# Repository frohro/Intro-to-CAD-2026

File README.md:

# Intro-to-CAD-2026

QSD SDR receiver board (WWU Intro to CAD) with versioned hardware and software.

## Layout

```text
v0.1/                  # First board revision
  Hardware/            # KiCad project for v0.1
  Software/SDR/        # MicroPython, Soapy, firmware/
v0.2/                  # Second board revision (CJC5340 option, etc.)
  Hardware/            # KiCad project for v0.2
  Software/SDR/        # MicroPython, Soapy, firmware/
Docs/                  # Plans, credits, restore notes
```

Pick the **root folder that matches the PCB silkscreen / board revision** you have.

| Board | Open KiCad | Software |
|-------|------------|----------|
| v0.1 | [v0.1/Hardware/Intro-to-CAD-2026.kicad_pro](v0.1/Hardware/Intro-to-CAD-2026.kicad_pro) | [v0.1/Software/SDR](v0.1/Software/SDR) |
| v0.2 | [v0.2/Hardware/Intro-to-CAD-2026.kicad_pro](v0.2/Hardware/Intro-to-CAD-2026.kicad_pro) | [v0.2/Software/SDR](v0.2/Software/SDR) |

Duplication between `v0.1` and `v0.2` is intentional so each board is self-contained.

## Firmware

Native Pico UAC1 projects live under each version's `Software/SDR/firmware/`.
Preferred v0.2 entry point: `v0.2/Software/SDR/firmware/2026_v0.2/`.
Re-sync notes: [Docs/FIRMWARE_RESTORE.md](Docs/FIRMWARE_RESTORE.md).

## History

- Tag `archive/pre-version-split` — layout before this reorg (student `Module_*` at repo root).
- Long-lived git branch `v0.2` held hardware work before the monorepo split; prefer paths under `v0.2/` on `master` going forward.
- Student module credits: [Docs/CREDITS.md](Docs/CREDITS.md).

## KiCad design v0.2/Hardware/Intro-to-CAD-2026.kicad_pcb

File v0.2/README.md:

# Board v0.2

## Hardware

Open [`Hardware/Intro-to-CAD-2026.kicad_pro`](Hardware/Intro-to-CAD-2026.kicad_pro).

Includes dual-ADC options (PCM1808 preferred; CJC5340 retained). Instructor
`Hardware/Frohne/` libs remain because the merged schematic references them.

## Software

| Path | Role |
|------|------|
| `Software/SDR/MicroPythonSDR/` | Pico MicroPython + Quisk helpers |
| `Software/SDR/Soapy-For-2026-Board/` | Soapy module |
| `Software/SDR/firmware/` | C UAC1 firmwares (PCM1808, CJC, Multi) — restore if empty |

Preferred firmware entry point once restored: `firmware/2026_v0.2/` (PCM1808 48/96).
CJC and Multi trees are kept for research even if PCM1808 is preferred on the bench.

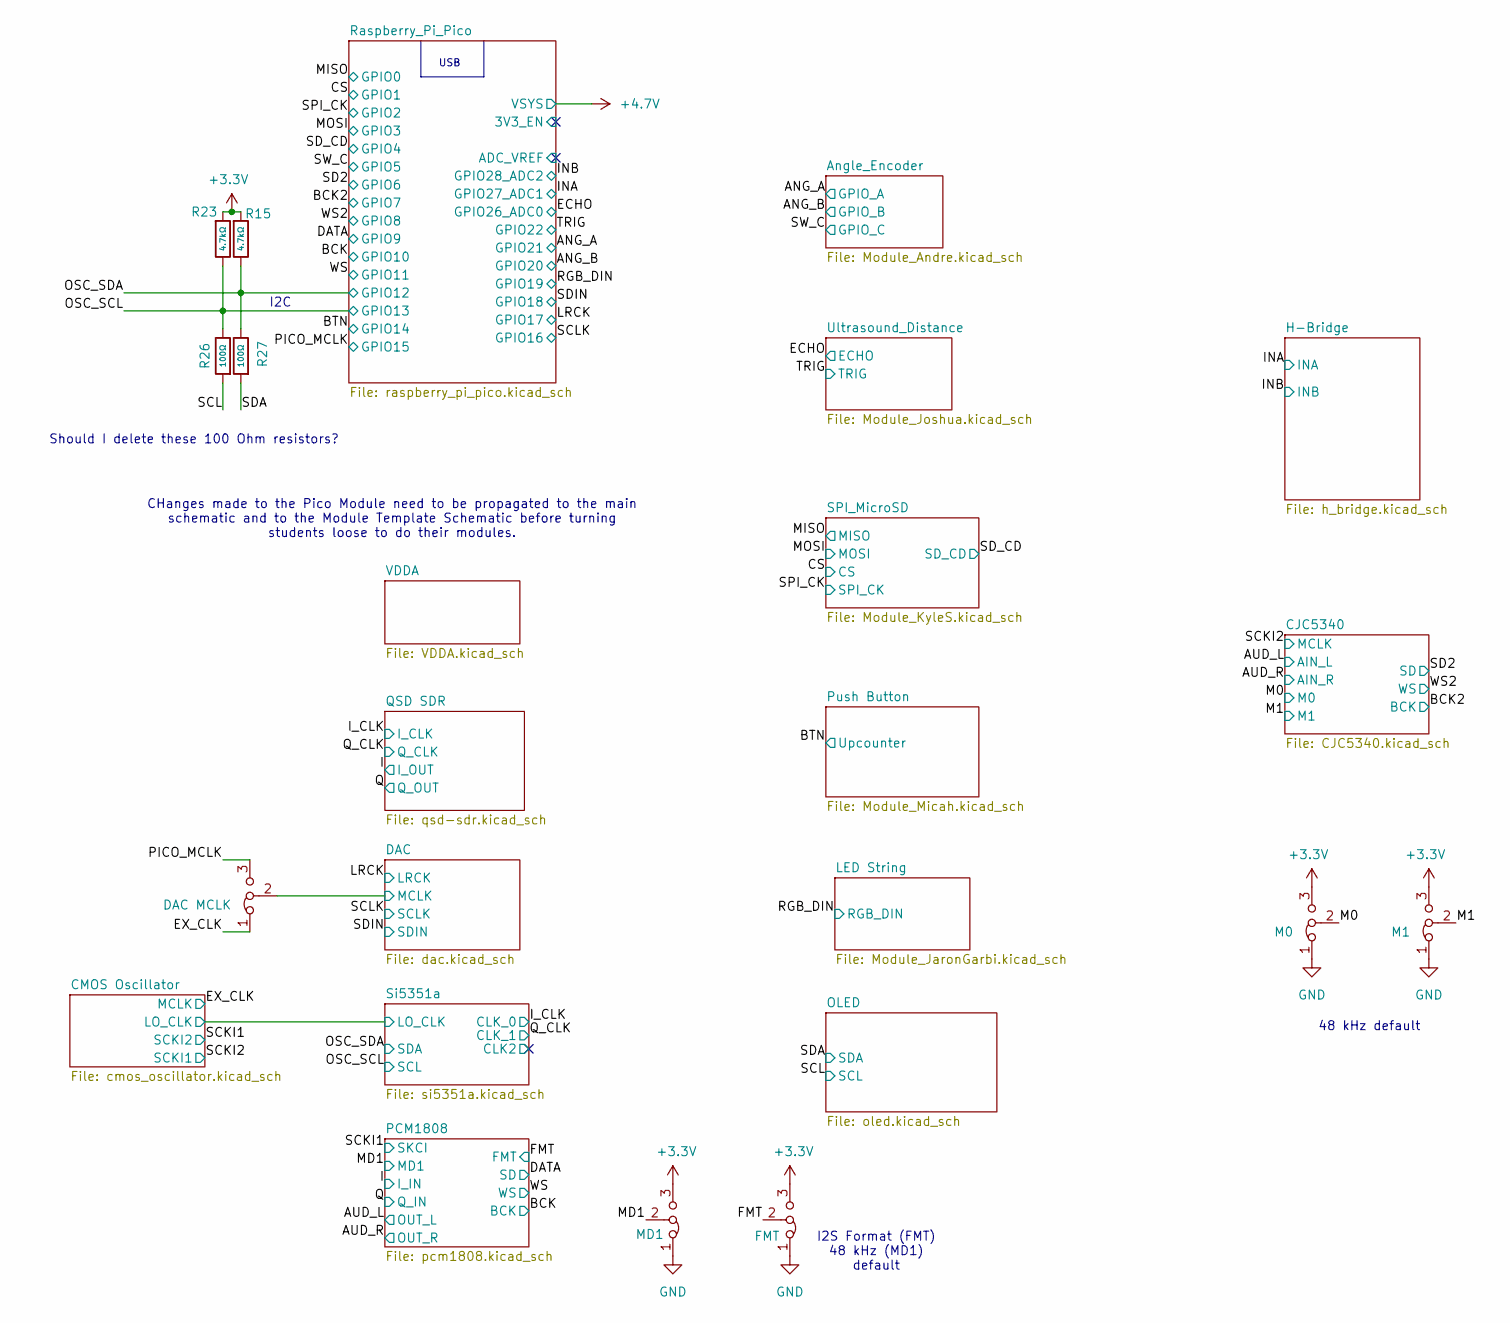
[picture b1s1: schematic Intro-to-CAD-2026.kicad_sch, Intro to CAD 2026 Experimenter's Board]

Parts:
JP6: DAC MCLK; SolderJumper-3_P1.3mm_Bridged12_RoundedPad1.0x1.5mm_NumberL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
JP11: M0; SolderJumper-3_P1.3mm_Bridged12_RoundedPad1.0x1.5mm_NumberL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
JP12: M1; SolderJumper-3_P1.3mm_Bridged12_RoundedPad1.0x1.5mm_NumberL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
JP13: FMT; SolderJumper-3_P1.3mm_Bridged12_RoundedPad1.0x1.5mm_NumberL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
JP14: MD1; SolderJumper-3_P1.3mm_Bridged12_RoundedPad1.0x1.5mm_NumberL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
R15, R23: 4.7kΩ; R_0805; Overload Voltage (Max) 150V; Tolerance ±1%; Part 0805W8F4701T5E; LCSC C17673
R26, R27: 100Ω; R_0805; Overload Voltage (Max) 150V; Tolerance ±1%; Part 0805W8F1000T5E; LCSC C17408

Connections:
+3.3V: JP11.3 (B), JP12.3 (B), JP13.3 (B), JP14.3 (B), R15.1, R23.1; also elsewhere on the board
/DAC/MCLK: JP6.2 (C); also elsewhere on the board
/EX_CLK: JP6.1 (A); also elsewhere on the board
/FMT: JP13.2 (C); also elsewhere on the board
/M0: JP11.2 (C); also elsewhere on the board
/M1: JP12.2 (C); also elsewhere on the board
/MD1: JP14.2 (C); also elsewhere on the board
/OSC_SCL: R23.2, R26.2; also elsewhere on the board
/OSC_SDA: R15.2, R27.2; also elsewhere on the board
/PICO_MCLK: JP6.3 (B); also elsewhere on the board
/SCL: R26.1; also elsewhere on the board
/SDA: R27.1; also elsewhere on the board
GND: JP11.1 (A), JP12.1 (A), JP13.1 (A), JP14.1 (A); also elsewhere on the board

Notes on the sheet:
CHanges made to the Pico Module need to be propagated to the main schematic and to the Module Template Schematic before turning students loose to do their modules.
Should I delete these 100 Ohm resistors?
I2S Format (FMT) 48 kHz (MD1) default
I2C
USB
48 kHz default

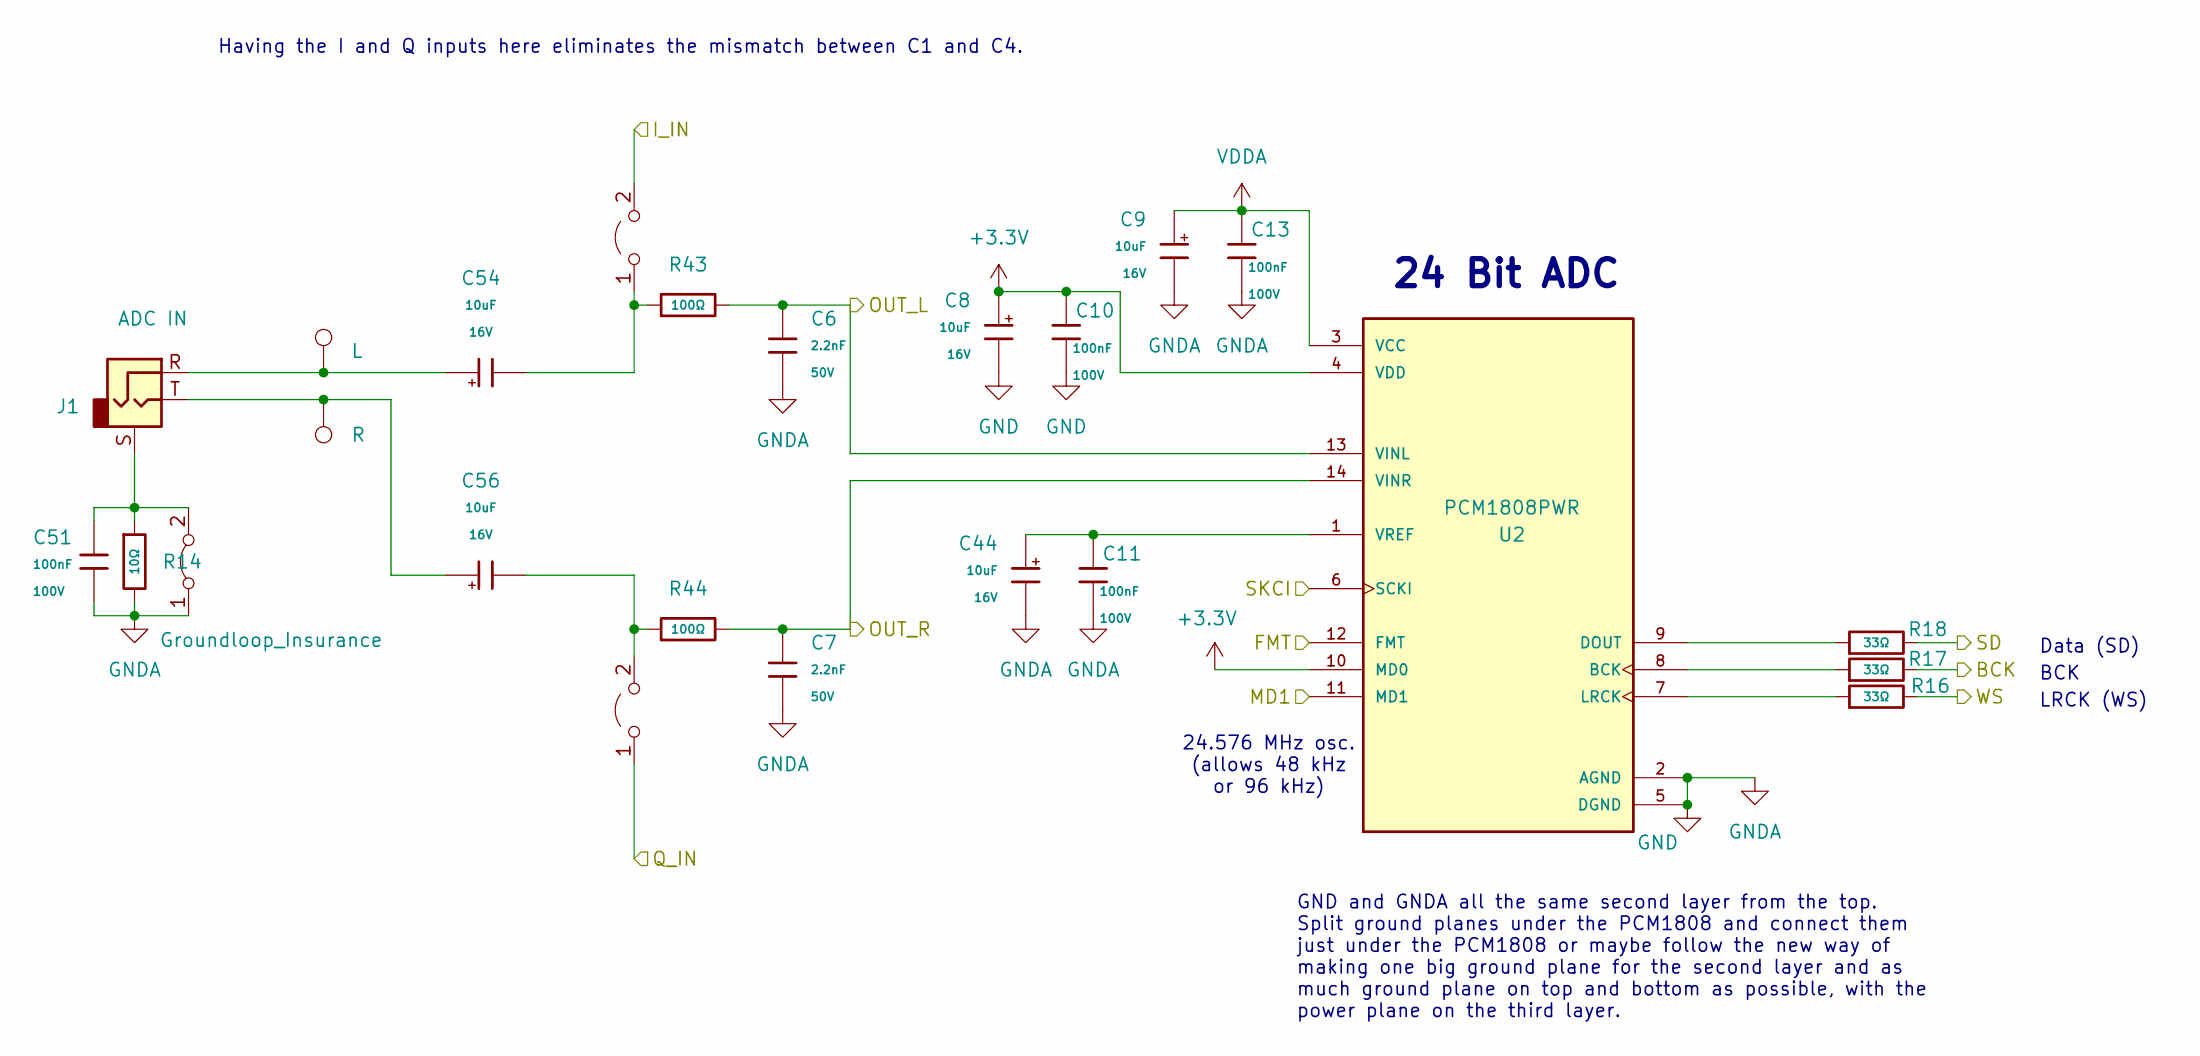
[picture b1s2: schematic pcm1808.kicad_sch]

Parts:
C6, C7: 2.2nF; C_0805; Voltage Rated 50V; Tolerance ±5%; Part CL21C222JBFNNNE; LCSC C28260
C8, C9, C44, C54, C56: 10uF; C_CASE-A-3216-18(mm); Tolerance ±10%; Rated Voltage 16V; Part TAJA106K016RNJ; LCSC C7171
C10, C11, C13, C51: 100nF; C_0805; Voltage Rated 100V; Tolerance ±10%; Part CL21B104KCFNNNE; LCSC C28233
J1: ADC IN; Jack_3.5mm_CUI_SJ-3523-SMT_Horizontal; LCSC C18594
JP18: I->ADC; SolderJumper-2_P1.3mm_Open_RoundedPad1.0x1.5mm
JP19: Q->ADC; SolderJumper-2_P1.3mm_Open_RoundedPad1.0x1.5mm
R14: 10Ω; R_0603; Overload Voltage (Max) 75V; Tolerance ±1%; Part 0603WAF100JT5E; LCSC C22859
R16, R17, R18: 33Ω; R_0805; Overload Voltage (Max) 150V; Tolerance ±1%; Part 0805W8F330JT5E; LCSC C17634
R43, R44: 100Ω; R_0603; Overload Voltage (Max) 75V; Tolerance ±1%; Part 0603WAF1000T5E; LCSC C22775
TP1: L; TestPoint_THTPad_D2.0mm_Drill1.0mm
TP2: R; TestPoint_THTPad_D2.0mm_Drill1.0mm
U2: PCM1808PWR; TSSOP-14_4.4x5mm_P0.65mm; PARTREV B; LCSC C55513
e4: Groundloop_Insurance; SolderJumper-2_P1.3mm_Bridged_RoundedPad1.0x1.5mm

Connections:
+3.3V: C8.1, C10.2, U2.4 (VDD), U2.10 (MD0); also elsewhere on the board
/AUD_L: C6.1, R43.2, U2.13 (VINL); also elsewhere on the board
/AUD_R: C7.1, R44.2, U2.14 (VINR); also elsewhere on the board
/BCK: R17.2; also elsewhere on the board
/DATA: R18.2; also elsewhere on the board
/FMT: U2.12 (FMT); also elsewhere on the board
/I: JP18.2 (B); also elsewhere on the board
/MD1: U2.11 (MD1); also elsewhere on the board
/Q: JP19.1 (A); also elsewhere on the board
/SCKI1: U2.6 (SCKI); also elsewhere on the board
/WS: R16.2; also elsewhere on the board
GND: C6.2, C7.2, C8.2, C9.2, C10.1, C11.1, C13.1, C44.2, C51.1, R14.2, U2.2 (AGND), U2.5 (DGND), e4.1 (A); also elsewhere on the board
unnamed: C54.1, J1.R, TP1.1 (1_1)
unnamed: C56.1, J1.T, TP2.1 (1_1)
unnamed: C54.2, JP18.1 (A), R43.1
unnamed: C56.2, JP19.2 (B), R44.1
unnamed: R17.1, U2.8 (BCK)
unnamed: R18.1, U2.9 (DOUT)
unnamed: R16.1, U2.7 (LRCK)
unnamed: C11.2, C44.1, U2.1 (VREF)
unnamed: C51.2, J1.S, R14.1, e4.2 (B)
VDDA: C9.1, C13.2, U2.3 (VCC); also elsewhere on the board

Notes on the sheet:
24 Bit ADC
Data (SD)
24.576 MHz osc. (allows 48 kHz or 96 kHz)
BCK
GND and GNDA all the same second layer from the top. Split ground planes under the PCM1808 and connect them just under the PCM1808 or maybe follow the new way of making one big ground plane for the second layer and as much ground plane on top and bottom as possible, with the power plane on the thir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
Having the I and Q inputs here eliminates the mismatch between C1 and C4.
LRCK (WS)

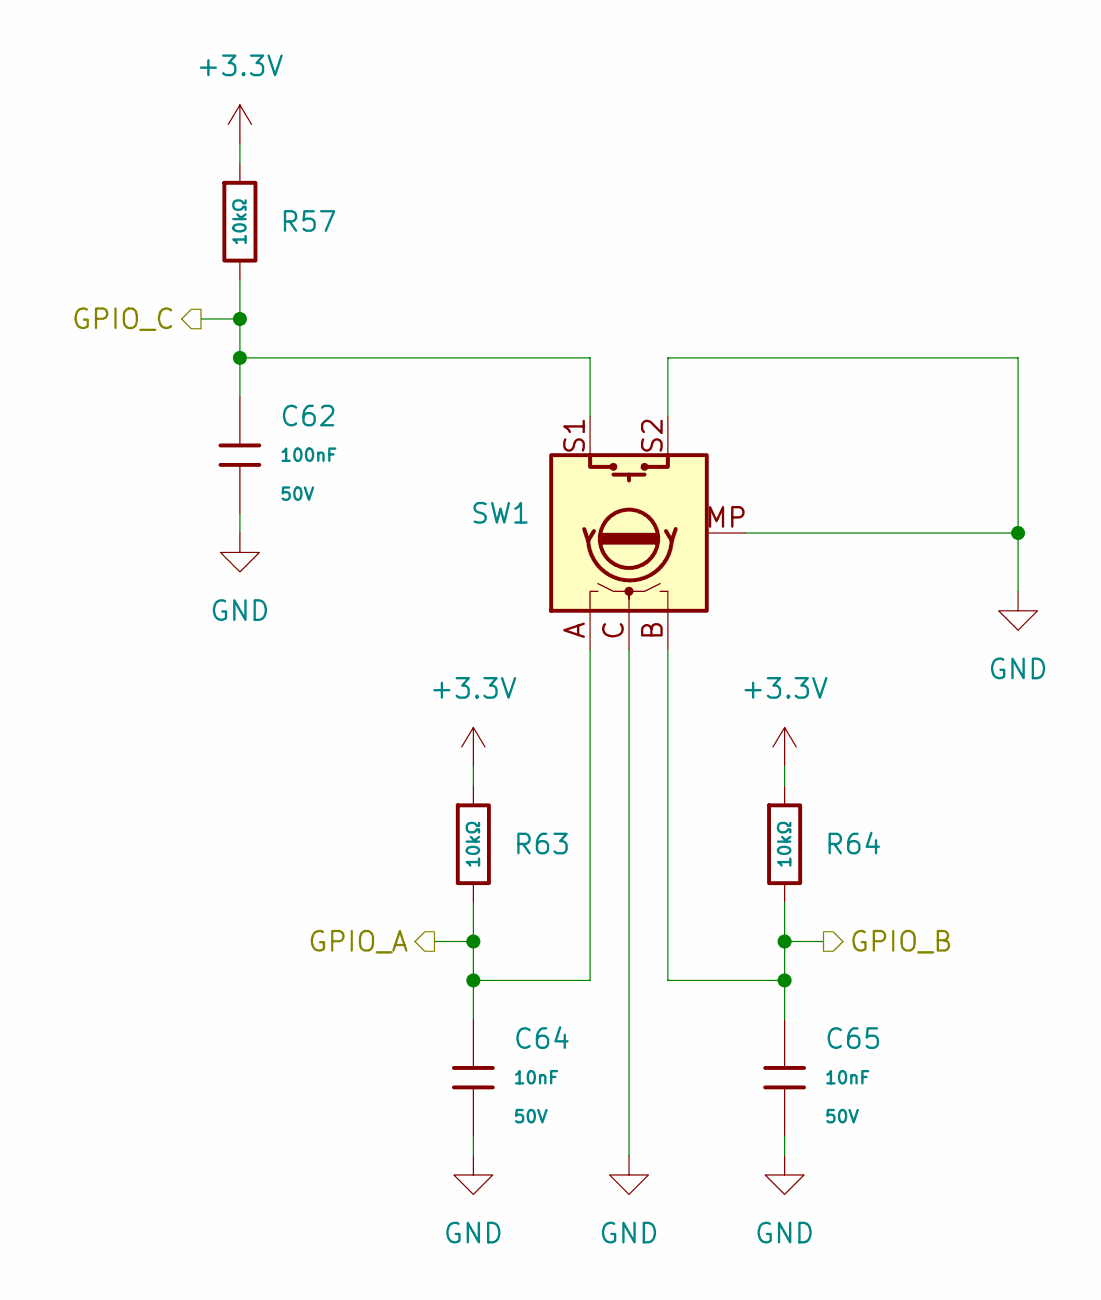
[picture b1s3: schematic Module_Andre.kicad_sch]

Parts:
C62: 100nF; C_0402; Voltage Rated 50V; Tolerance ±10%; Part CL05B104KB54PNC; LCSC C307331
C64, C65: 10nF; C_0402; Voltage Rated 50V; Tolerance ±10%; Part CL05B103KB5NNNC; LCSC C15195
R57, R63, R64: 10kΩ; R_0402; Overload Voltage (Max) 50V; Tolerance ±1%; Part 0402WGF1002TCE; LCSC C25744
SW1: RotaryEncoder_Switch_MP; RotaryEncoder_Alps_EC11E-Switch_Vertical_H20mm; LCSC C202365

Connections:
+3.3V: R57.1, R63.1, R64.1; also elsewhere on the board
/ANG_A: C64.1, R63.2, SW1.A; also elsewhere on the board
/ANG_B: C65.1, R64.2, SW1.B; also elsewhere on the board
/SW_C: C62.1, R57.2, SW1.S1; also elsewhere on the board
GND: C62.2, C64.2, C65.2, SW1.C, SW1.MP, SW1.S2; also elsewhere on the board

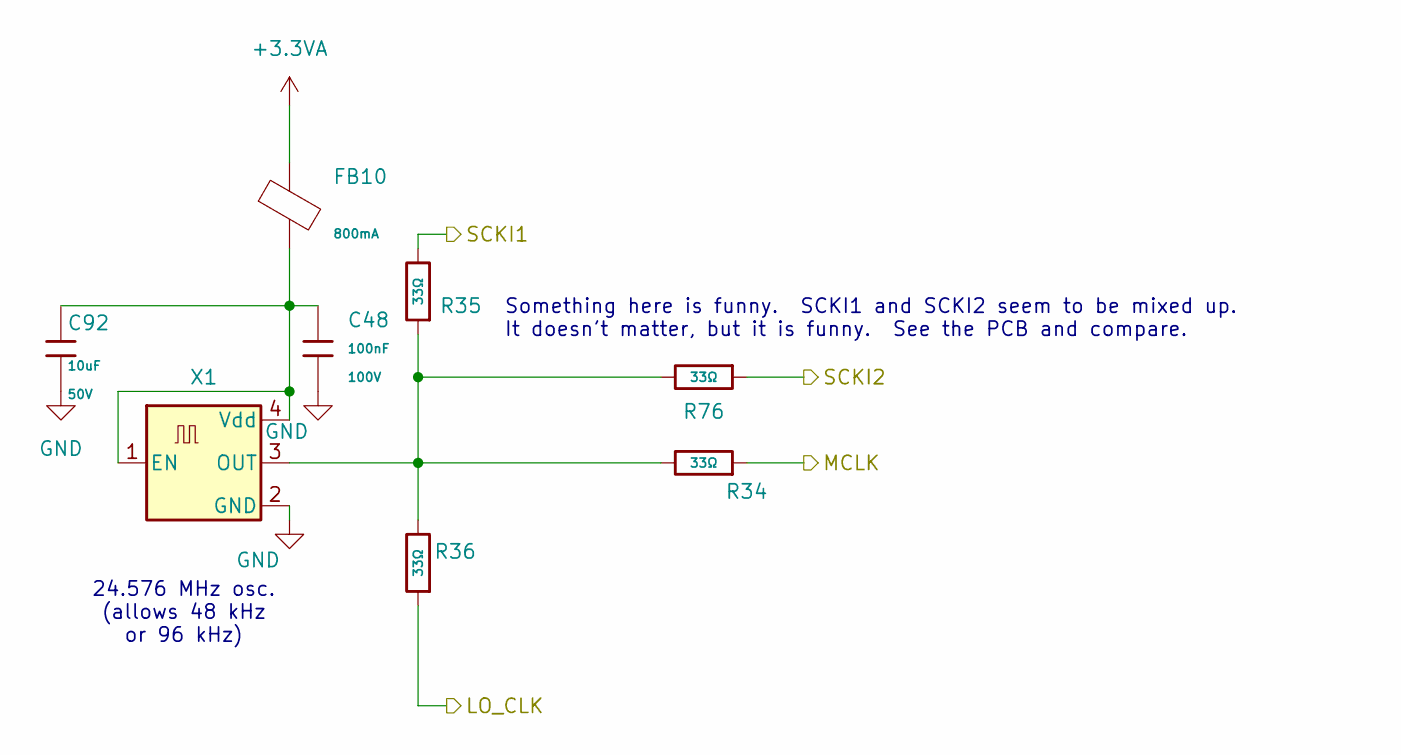
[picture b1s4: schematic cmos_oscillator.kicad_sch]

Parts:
C48: 100nF; C_0805; Voltage Rated 100V; Tolerance ±10%; Part CL21B104KCFNNNE; LCSC C28233
C92: 10uF; C_1206; Voltage Rated 50V; Tolerance ±10%; Part CL31A106KBHNNNE; LCSC C13585
FB10: FB_0805; Current Rating 800mA; Tolerance ±25%; Part GZ2012D101TF; LCSC C1015
R34, R35, R36, R76: 33Ω; R_0805; Overload Voltage (Max) 150V; Tolerance ±1%; Part 0805W8F330JT5E; LCSC C17634
X1: YC24.576MUBCE2O; Oscillator_SMD_Abracon_ASE-4Pin_3.2x2.5mm; LCSC C52204801

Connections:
+3.3VA: FB10.1; also elsewhere on the board
/CMOS Oscillator/LO_CLK: R36.1; also elsewhere on the board
/EX_CLK: R34.1; also elsewhere on the board
/SCKI1: R76.1; also elsewhere on the board
/SCKI2: R35.2; also elsewhere on the board
GND: C48.2, C92.2, X1.2 (GND); also elsewhere on the board
unnamed: C48.1, C92.1, FB10.2, X1.1 (EN), X1.4 (Vdd)
unnamed: R34.2, R35.1, R36.2, R76.2, X1.3 (OUT)

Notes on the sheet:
Something here is funny. SCKI1 and SCKI2 seem to be mixed up. It doesn't matter, but it is funny. See the PCB and compare.
24.576 MHz osc. (allows 48 kHz or 96 kHz)

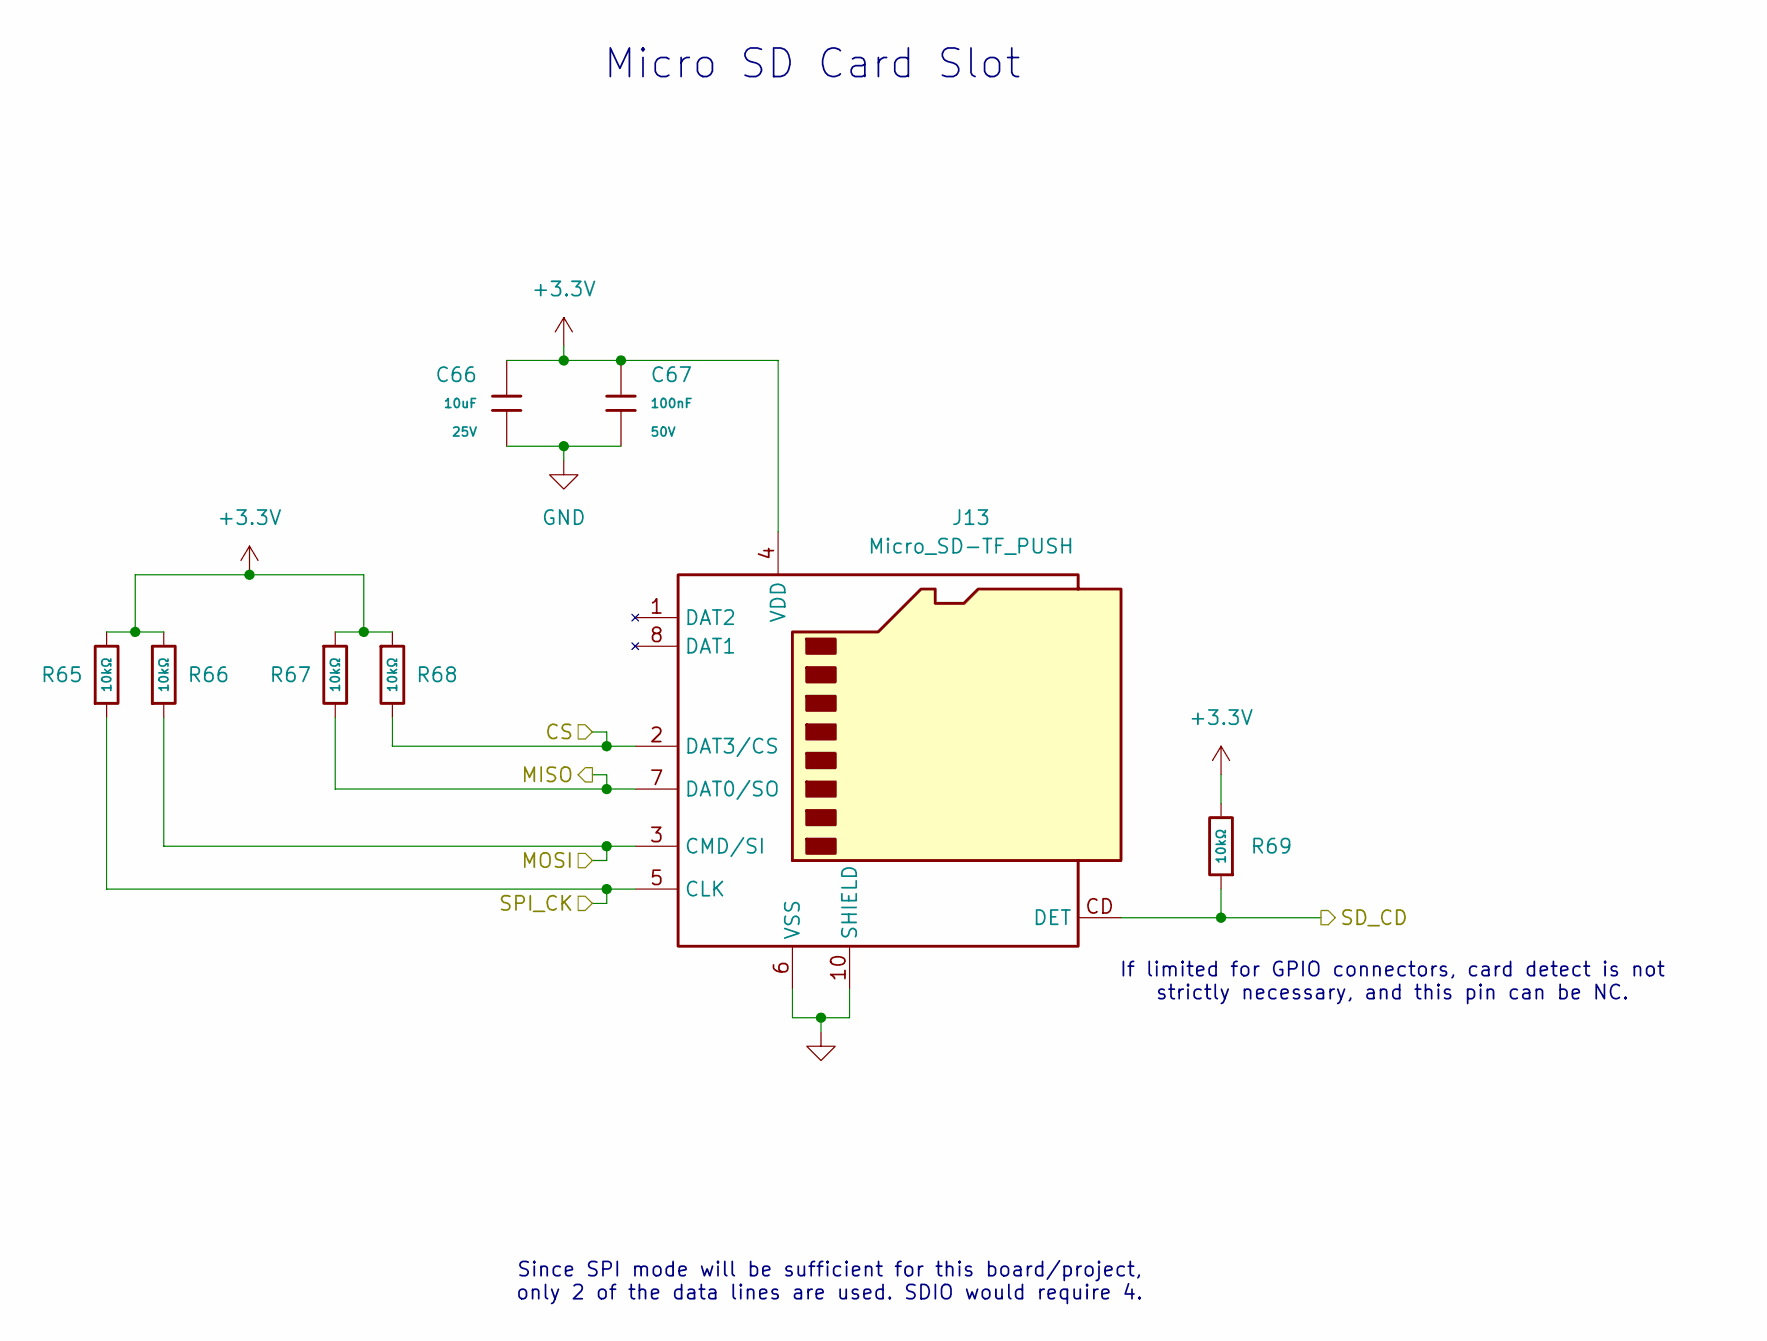
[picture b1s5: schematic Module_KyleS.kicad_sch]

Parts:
C66: 10uF; C_0805; Voltage Rated 25V; Tolerance ±10%; Part CL21A106KAYNNNE; LCSC C15850
C67: 100nF; C_0603; Voltage Rated 50V; Tolerance ±10%; Part CC0603KRX7R9BB104; LCSC C14663
J13: Micro_SD-TF_PUSH; TF-SMD_TF-PUSH; LCSC C393941
R65, R66, R67, R68, R69: 10kΩ; R_0603; Overload Voltage (Max) 75V; Tolerance ±1%; Part 0603WAF1002T5E; LCSC C25804

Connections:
+3.3V: C66.1, C67.1, J13.4 (VDD), R65.2, R66.2, R67.1, R68.1, R69.2; also elsewhere on the board
/CS: J13.2 (DAT3/CS), R68.2; also elsewhere on the board
/MISO: J13.7 (DAT0/SO), R67.2; also elsewhere on the board
/MOSI: J13.3 (CMD/SI), R66.1; also elsewhere on the board
/SD_CD: J13.CD (DET), R69.1; also elsewhere on the board
/SPI_CK: J13.5 (CLK), R65.1; also elsewhere on the board
GND: C66.2, C67.2, J13.6 (VSS), J13.10 (SHIELD), J13.11 (SHIELD), J13.12 (SHIELD), J13.13 (SHIELD); also elsewhere on the board

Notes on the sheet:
Since SPI mode will be sufficient for this board/project, only 2 of the data lines are used. SDIO would require 4.
Micro SD Card Slot
If limited for GPIO connectors, card detect is not strictly necessary, and this pin can be NC.

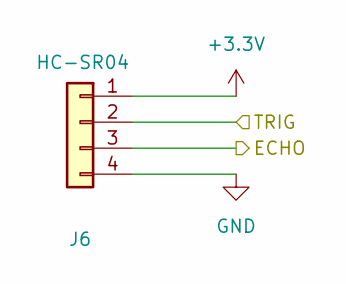
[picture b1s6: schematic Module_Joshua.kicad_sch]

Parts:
J6: HC-SR04; PinSocket_1x04_P2.54mm_Vertical; LCSC C2718488

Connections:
+3.3V: J6.1; also elsewhere on the board
/ECHO: J6.3; also elsewhere on the board
/TRIG: J6.2; also elsewhere on the board
GND: J6.4; also elsewhere on the board

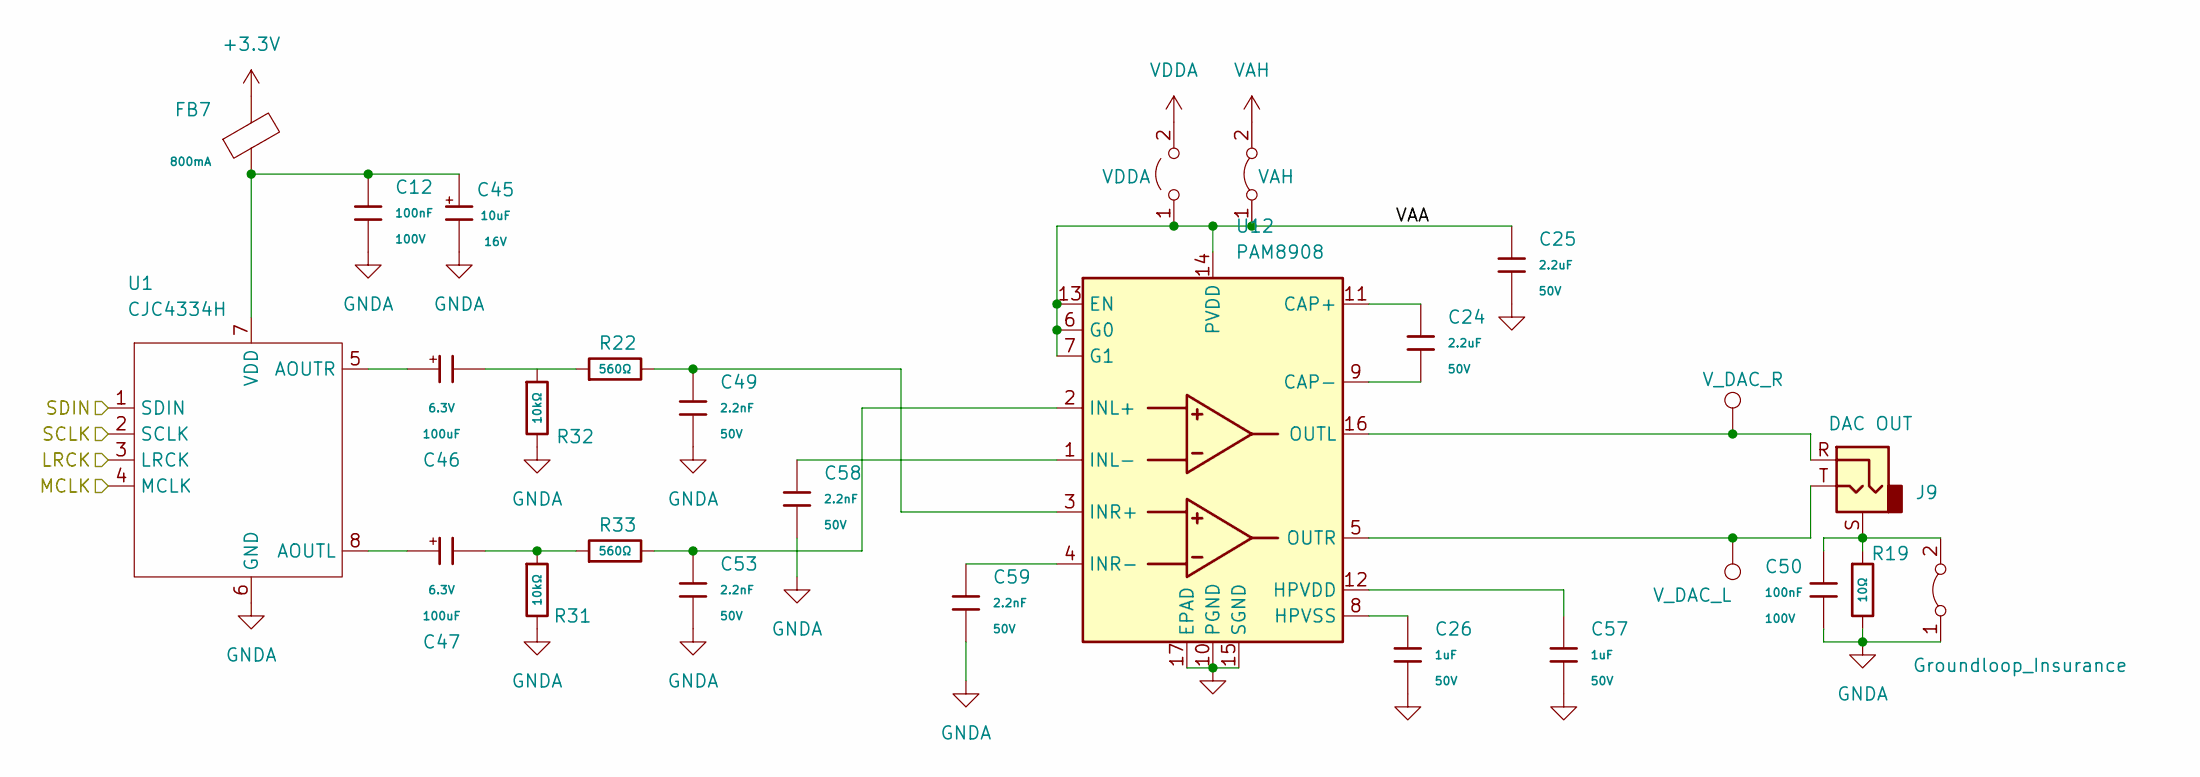
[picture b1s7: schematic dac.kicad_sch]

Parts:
C12, C50: 100nF; C_0805; Voltage Rated 100V; Tolerance ±10%; Part CL21B104KCFNNNE; LCSC C28233
C24, C25: 2.2uF; C_0805; Voltage Rated 50V; Tolerance ±10%; Part CL21A225KBQNNNE; LCSC C377773
C26, C57: 1uF; C_0805; Voltage Rated 50V; Tolerance ±10%; Part CL21B105KBFNNNE; LCSC C28323
C45: 10uF; C_CASE-A-3216-18(mm); Tolerance ±10%; Rated Voltage 16V; Part TAJA106K016RNJ; LCSC C7171
C46, C47: 100uF; C_CASE-B-3528-21(mm); Tolerance ±10%; Rated Voltage 6.3V; Part TAJB107K006RNJ; LCSC C16133
C49, C53, C58, C59: 2.2nF; C_0805; Voltage Rated 50V; Tolerance ±5%; Part CL21C222JBFNNNE; LCSC C28260
FB7: FB_0805; Current Rating 800mA; Tolerance ±25%; Part GZ2012D101TF; LCSC C1015
J9: 3.5mm_Jack; Jack_3.5mm_CUI_SJ-3523-SMT_Horizontal; LCSC C18594
JP3: VDDA; SolderJumper-2_P1.3mm_Open_RoundedPad1.0x1.5mm
R19: 10Ω; R_0603; Overload Voltage (Max) 75V; Tolerance ±1%; Part 0603WAF100JT5E; LCSC C22859
R22, R33: 560Ω; R_0805; Overload Voltage (Max) 150V; Tolerance ±1%; Part 0805W8F5600T5E; LCSC C28636
R31, R32: 10kΩ; R_0805; Overload Voltage (Max) 150V; Tolerance ±1%; Part 0805W8F1002T5E; LCSC C17414
TP8: V_DAC_R; TestPoint_THTPad_D2.0mm_Drill1.0mm
TP9: V_DAC_L; TestPoint_THTPad_D2.0mm_Drill1.0mm
U1: CJC4334H; SOIC-8_3.9x4.9mm_P1.27mm; LCSC C41417670
U12: PAM8908; QFN-16-1EP_3x3mm_P0.5mm_EP1.7x1.7mm; LCSC C33233
e2: VAH; SolderJumper-2_P1.3mm_Bridged_RoundedPad1.0x1.5mm
e3: Groundloop_Insurance; SolderJumper-2_P1.3mm_Bridged_RoundedPad1.0x1.5mm

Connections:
+3.3V: FB7.2; also elsewhere on the board
+4.7V: e2.2 (B); also elsewhere on the board
/DAC/MCLK: U1.4 (MCLK); also elsewhere on the board
/DAC/VAA: C25.1, JP3.1 (A), U12.6 (G0), U12.7 (G1), U12.13 (EN), U12.14 (PVDD), e2.1 (A)
/LRCK: U1.3 (LRCK); also elsewhere on the board
/SCLK: U1.2 (SCLK); also elsewhere on the board
/SDIN: U1.1 (SDIN); also elsewhere on the board
GND: C12.2, C25.2, C26.2, C45.2, C49.2, C50.1, C53.2, C57.2, C58.2, C59.2, R19.2, R31.2, R32.2, U1.6 (GND), U12.10 (PGND), U12.15 (SGND), U12.17 (EPAD), e3.1 (A); also elsewhere on the board
unnamed: C46.2, R22.1
unnamed: C47.2, R31.1, R33.1
unnamed: C47.1, U1.8 (AOUTL)
unnamed: C46.1, U1.5 (AOUTR)
unnamed: C12.1, C45.1, FB7.1, U1.7 (VDD)
unnamed: C24.1, U12.11 (CAP+)
unnamed: C24.2, U12.9 (CAP-)
unnamed: C57.1, U12.12 (HPVDD)
unnamed: C26.1, U12.8 (HPVSS)
unnamed: C53.1, R33.2, U12.2 (INL+)
unnamed: C58.1, U12.1 (INL-)
unnamed: C49.1, R22.2, U12.3 (INR+)
unnamed: C59.1, U12.4 (INR-)
unnamed: J9.R, TP8.1 (1_1), U12.16 (OUTL)
unnamed: J9.T, TP9.1 (1_1), U12.5 (OUTR)
unnamed: C50.2, J9.S, R19.1, e3.2 (B)
VDDA: JP3.2 (B); also elsewhere on the board

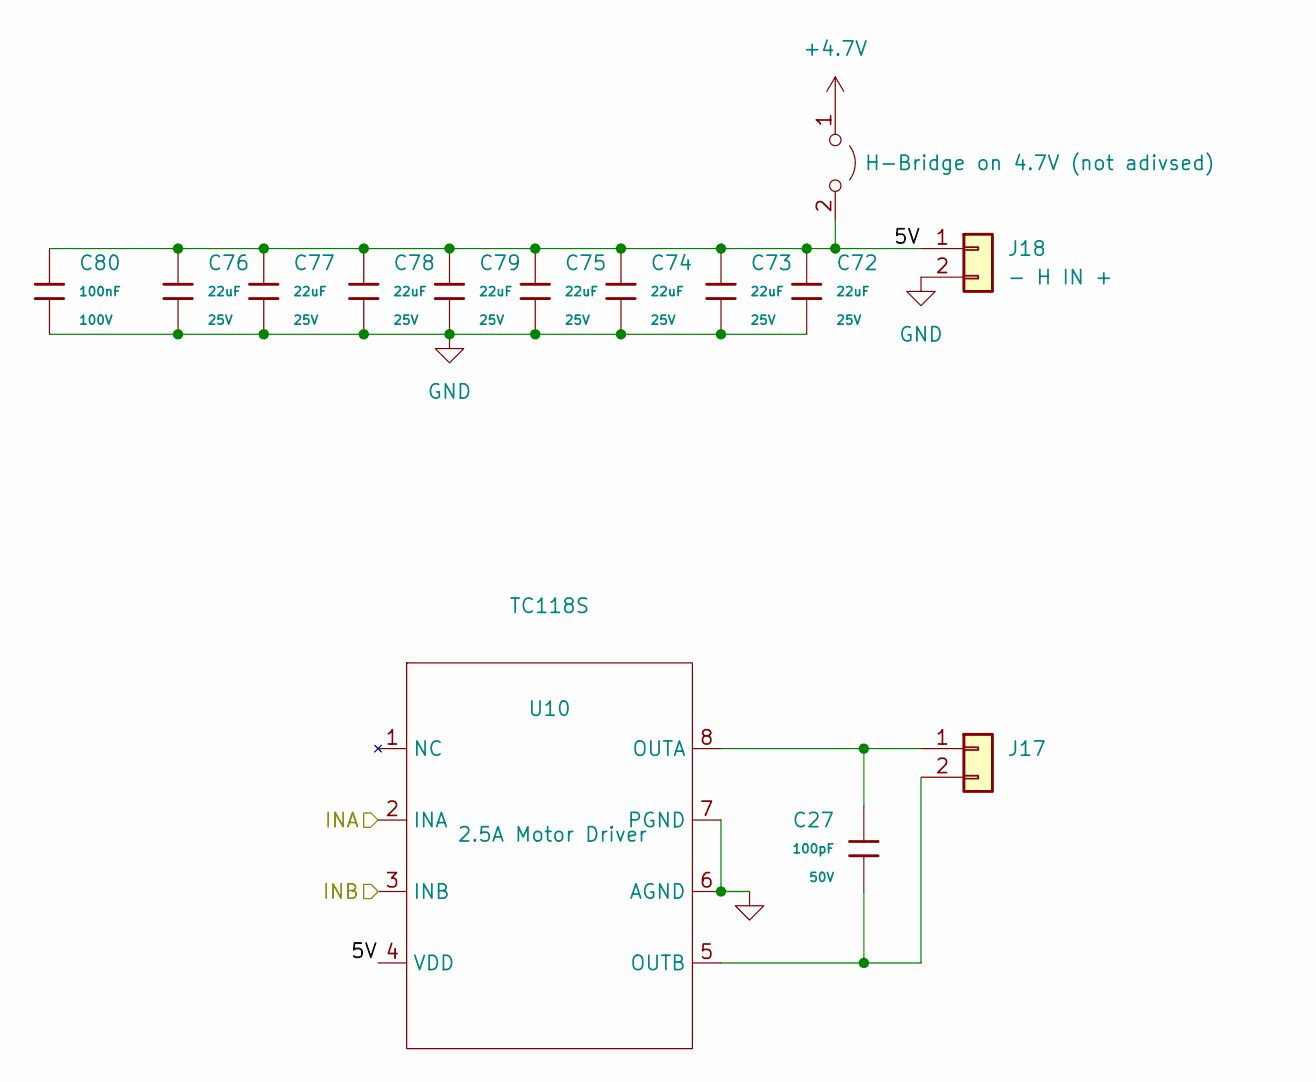
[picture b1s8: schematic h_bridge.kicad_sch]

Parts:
C27: 100pF; C_0402; Voltage Rated 50V; Tolerance ±5%; Part 0402CG101J500NT; LCSC C1546
C72, C73, C74, C75, C76, C77, C78, C79: 22uF; C_0805; Voltage Rated 25V; Tolerance ±20%; Part CL21A226MAQNNNE; LCSC C45783
C80: 100nF; C_0805; Voltage Rated 100V; Tolerance ±10%; Part CL21B104KCFNNNE; LCSC C28233
J17: H OUT; TerminalBlock_Phoenix_MKDS-1,5-2-5.08_1x02_P5.08mm_Horizont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; LCSC C8465
J18: - H IN +; TerminalBlock_Phoenix_MKDS-1,5-2-5.08_1x02_P5.08mm_Horizont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; LCSC C8465
JP4: H-Bridge on 4.7V (not adivsed); SolderJumper-2_P1.3mm_Open_RoundedPad1.0x1.5mm
U10: TC118S; SOP-8_3.76x4.96mm_P1.27mm; LCSC C88308

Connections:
+4.7V: JP4.1 (A); also elsewhere on the board
/H-Bridge/5V: C72.1, C73.1, C74.1, C75.1, C76.1, C77.1, C78.1, C79.1, C80.1, J18.1, JP4.2 (B), U10.4 (VDD)
/INA: U10.2 (INA); also elsewhere on the board
/INB: U10.3 (INB); also elsewhere on the board
GND: C72.2, C73.2, C74.2, C75.2, C76.2, C77.2, C78.2, C79.2, C80.2, J18.2, U10.6 (AGND), U10.7 (PGND); also elsewhere on the board
unnamed: C27.1, J17.1, U10.8 (OUTA)
unnamed: C27.2, J17.2, U10.5 (OUTB)

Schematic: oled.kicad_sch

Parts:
J15: OLED; PinSocket_1x04_P2.54mm_Vertical; LCSC C2718488

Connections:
+3.3V: J15.2; also elsewhere on the board
/SCL: J15.3; also elsewhere on the board
/SDA: J15.4; also elsewhere on the board
GND: J15.1; also elsewhere on the board

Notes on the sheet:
Be careful! Some OLEDs have Vcc and GND swapped! These are in the order GND-Vcc-SCL-SDA.

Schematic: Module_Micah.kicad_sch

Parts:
R70: 10kΩ; R_0402; Overload Voltage (Max) 50V; Tolerance ±1%; Part 0402WGF1002TCE; LCSC C25744
S2: Tactile Button, 160gf; SW_TS-1088-AR02016; Voltage Rating (Dc) 12V; Part TS-1088-AR02016; LCSC C720477

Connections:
+3.3V: R70.1; also elsewhere on the board
/BTN: R70.2, S2.2 (B); also elsewhere on the board
GND: S2.1 (A); also elsewhere on the board

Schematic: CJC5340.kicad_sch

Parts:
C3, C4, C104, C108, C113: 10uF; C_CASE-A-3216-18(mm); Tolerance ±10%; Rated Voltage 16V; Part TAJA106K016RNJ; LCSC C7171
C60, C61: 2.2nF; C_0805; Voltage Rated 50V; Tolerance ±5%; Part CL21C222JBFNNNE; LCSC C28260
C99: 100uF; C_CASE-B-3528-21(mm); Tolerance ±10%; Rated Voltage 6.3V; Part TAJB107K006RNJ; LCSC C16133
C106, C109, C110, C112, C114: 100nF; C_0805; Voltage Rated 100V; Tolerance ±10%; Part CL21B104KCFNNNE; LCSC C28233
R39, R40, R41, R42: 10kΩ; R_0402; Overload Voltage (Max) 50V; Tolerance ±1%; Part 0402WGF1002TCE; LCSC C25744
R75: 10kΩ; R_0805; Overload Voltage (Max) 150V; Tolerance ±1%; Part 0805W8F1002T5E; LCSC C17414
R78, R79: 33Ω; R_0805; Overload Voltage (Max) 150V; Tolerance ±1%; Part 0805W8F330JT5E; LCSC C17634
R81: 5.1Ω; R_0805; Overload Voltage (Max) 150V; Tolerance ±1%; Part 0805W8F510KT5E; LCSC C17724
U13: TSSOP-16_4.4x5mm_P0.65mm; Manufacturer Part CJC5340; LCSC Part Name 100dB、192kHz多bit 音频A/D转换器

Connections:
+3.3V: C104.1, C106.2, R75.2, R81.2, U13.3 (VL), U13.9 (RST#); also elsewhere on the board
+3.3VA: C108.1, C109.2, R39.1, R41.1, U13.13 (VA); also elsewhere on the board
/AUD_L: C3.1; also elsewhere on the board
/AUD_R: C4.1; also elsewhere on the board
/BCK2: R79.2; also elsewhere on the board
/M0: U13.1 (M0); also elsewhere on the board
/M1: U13.16 (M1); also elsewhere on the board
/SCKI2: U13.2 (MCLK); also elsewhere on the board
/SD2: R75.1, R78.2; also elsewhere on the board
/WS2: U13.8 (LRCK); also elsewhere on the board
GND: C60.2, C61.2, C99.2, C104.2, C106.1, C108.2, C109.1, C110.1, C112.1, C113.2, C114.1, R40.2, R42.2, U13.5 (GND), U13.14 (GND); also elsewhere on the board
unnamed: C3.2, C60.1, R39.2, R40.1, U13.10 (AINL)
unnamed: C4.2, C61.1, R41.2, R42.1, U13.12 (AINR)
unnamed: C99.1, C112.2, U13.15 (FILT+)
unnamed: R79.1, U13.7 (SCLK)
unnamed: R78.1, U13.4 (SDOUT)
unnamed: C110.2, R81.1, U13.6 (VD)
unnamed: C113.1, C114.2, U13.11 (VQ)

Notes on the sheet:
Double speed slave made (96 kHz). To select 48 kHz, M0 needs to be set low. For 192 kHz, both have to be high.
24.576 MHz osc.
Data (SD)
The CS5340 will work on 5V, but not the CJT5340!
for I2S format.
Leave this out next time!
24 Bit ADC CDC5340

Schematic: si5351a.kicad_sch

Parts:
C15, C38: 100nF; C_0805; Voltage Rated 100V; Tolerance ±10%; Part CL21B104KCFNNNE; LCSC C28233
C34, C91: 10uF; C_1206; Voltage Rated 50V; Tolerance ±10%; Part CL31A106KBHNNNE; LCSC C13585
C84: 100uF; C_CASE-B-3528-21(mm); Tolerance ±10%; Rated Voltage 6.3V; Part TAJB107K006RNJ; LCSC C16133
FB1, FB4: FB_0805; Current Rating 800mA; Tolerance ±25%; Part GZ2012D101TF; LCSC C1015
JP7, JP8: Johnson Counter?; SolderJumper-3_P1.3mm_Bridged12_RoundedPad1.0x1.5mm_NumberL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
R37, R38, R72: 33Ω; R_0805; Overload Voltage (Max) 150V; Tolerance ±1%; Part 0805W8F330JT5E; LCSC C17634
R74: 1Ω; R_0805; Overload Voltage (Max) 150V; Tolerance ±1%; Part 0805W8F100KT5E; LCSC C25271
TP3: I LO; TestPoint_THTPad_D2.0mm_Drill1.0mm
TP4: Q LO; TestPoint_THTPad_D2.0mm_Drill1.0mm
TP5: OSC; TestPoint_THTPad_D2.0mm_Drill1.0mm
U4: MS5351M; MSOP-10_3x3mm_P0.5mm; LCSC C1509083
U11: SN74LVC74ADR; SOIC-14_3.9x8.7mm_P1.27mm; LCSC C7864

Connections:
+3.3V: C84.1, R74.2; also elsewhere on the board
+3.3VA: FB4.2; also elsewhere on the board
/CMOS Oscillator/LO_CLK: U4.2 (XA); also elsewhere on the board
/I_CLK: R37.1, TP3.1 (1_1); also elsewhere on the board
/OSC_SCL: U4.4 (SCL); also elsewhere on the board
/OSC_SDA: U4.5 (SDA); also elsewhere on the board
/Q_CLK: R38.1, TP4.1 (1_1); also elsewhere on the board
/Si5351a/3.3VAO: C38.2, C91.1, FB1.2, U4.7 (VDDO), U11.1 (~R), U11.4 (~S), U11.10 (~S), U11.13 (~R), U11.14 (VCC)
GND: C15.1, C34.2, C38.1, C84.2, C91.2, U4.8 (GND), U11.7 (GND); also elsewhere on the board
unnamed: FB1.1, R74.1
unnamed: JP7.1 (A), U11.6 (~Q)
unnamed: JP7.3 (B), U4.10 (CLK0)
unnamed: JP7.2 (C), R37.2
unnamed: JP8.1 (A), U11.9 (Q)
unnamed: JP8.3 (B), U4.9 (CLK1)
unnamed: JP8.2 (C), R38.2
unnamed: R72.2, TP5.1 (1_1), U4.6 (CLK2)
unnamed: C15.2, C34.1, FB4.1, U4.1 (VDD)
unnamed: R72.1, U11.3 (C), U11.11 (C)
unnamed: U11.2 (D), U11.8 (~Q)
unnamed: U11.5 (Q), U11.12 (D)

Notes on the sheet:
Lay this out so the Johnson counter is right next to the MS5351a, or move the 33 Ohm resistors close to each possible driver for the I and Q clocks.
Johnson Counter for Quadrature
24.576 MHz
Oscillator
